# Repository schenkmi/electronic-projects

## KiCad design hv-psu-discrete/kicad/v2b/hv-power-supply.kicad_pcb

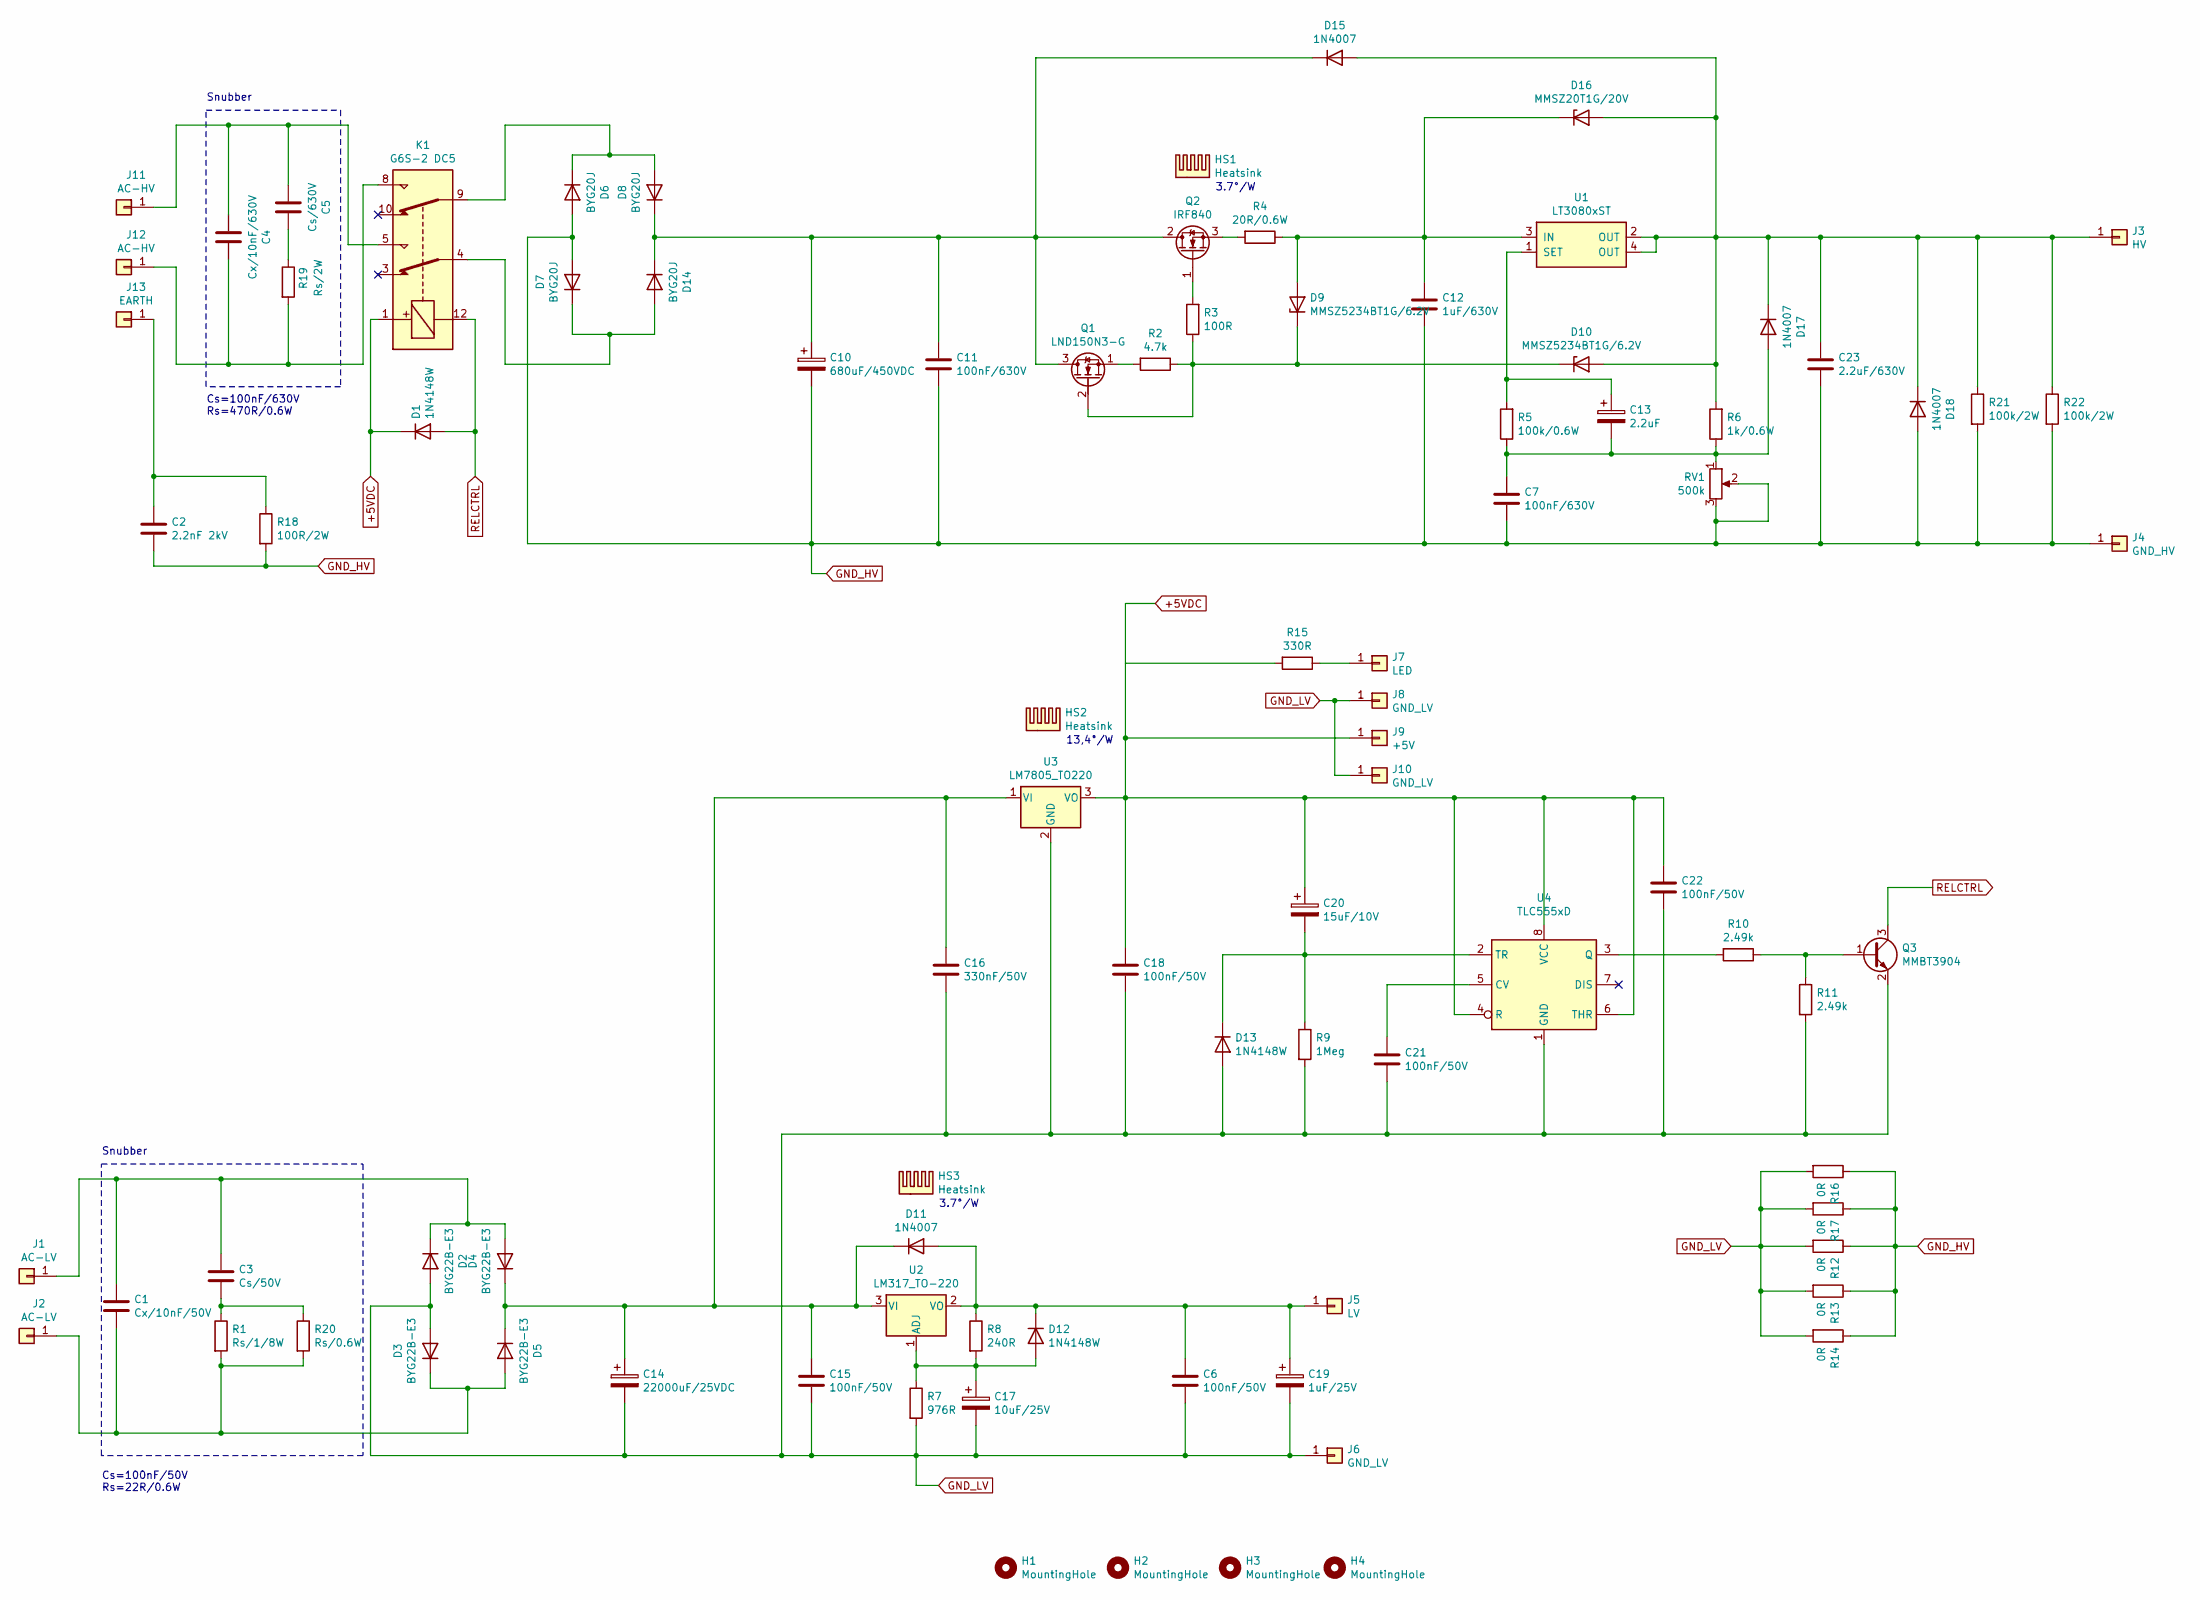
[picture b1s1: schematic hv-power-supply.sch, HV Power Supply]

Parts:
C1: Cx/10nF/50V; C_0805_2012Metric_Pad1.18x1.45mm_HandSolder
C2: 2.2nF 2kV; C_Rect_L18.0mm_W5.0mm_P15.00mm_FKS3_FKP3
C3: Cs/50V; C_0805_2012Metric_Pad1.18x1.45mm_HandSolder
C4: Cx/10nF/630V; C_Rect_L13.0mm_W4.0mm_P10.00mm_FKS3_FKP3_MKS4
C5: Cs/630V; C_Rect_L18.0mm_W5.0mm_P15.00mm_FKS3_FKP3
C6, C15, C18, C21, C22: 100nF/50V; C_0805_2012Metric_Pad1.18x1.45mm_HandSolder
C7, C11: 100nF/630V; C_Rect_L18.0mm_W5.0mm_P15.00mm_FKS3_FKP3
C10: 680uF/450VDC; CP_Radial_D35.0mm_P10.00mm_SnapIn
C12: 1uF/630V; C_Rect_L26.5mm_W10.5mm_P22.50mm_MKS4
C13: 2.2uF; CP_Radial_D5.0mm_P2.50mm
C14: 22000uF/25VDC; CP_Radial_D35.0mm_P10.00mm_SnapIn
C16: 330nF/50V; C_0805_2012Metric_Pad1.18x1.45mm_HandSolder
C17: 10uF/25V; CP_Radial_D5.0mm_P2.00mm
C19: 1uF/25V; CP_Radial_D5.0mm_P2.00mm
C20: 15uF/10V; CP_EIA-3216-12_Kemet-S_Pad1.58x1.35mm_HandSolder
C23: 2.2uF/630V; C_Rect_L33.0mm_W15.0mm_P27.50mm_MKS4
D1, D12, D13: 1N4148W; D_SOD-123
D2, D3, D4, D5: BYG22B-E3; D_SMA_Handsoldering
D6, D7, D8, D14: BYG20J; D_SMA_Handsoldering
D9, D10: MMSZ5234BT1G/6.2V; D_SOD-123
D11, D15, D17, D18: 1N4007; D_SMA_Handsoldering
D16: MMSZ20T1G/20V; D_SOD-123
H1, H2, H3, H4: MountingHole; MountingHole_3.2mm_M3
HS1, HS3: Heatsink; Heatsink_Fischer_SK129-STS_42x25mm_2xDrill2.5mm
HS2: Heatsink; Heatsink_Fischer_SK104-STC-STIC_35x13mm_2xDrill2.5mm
J1, J2: AC-LV; Pin_D1.3mm_L11.0mm
J3: HV; Pin_D1.3mm_L11.0mm
J4: GND_HV; Pin_D1.3mm_L11.0mm
J5: LV; Pin_D1.3mm_L11.0mm
J6: GND_LV; Pin_D1.3mm_L11.0mm
J7: LED; Pin_D1.0mm_L10.0mm
J8, J10: GND_LV; Pin_D1.0mm_L10.0mm
J9: +5V; Pin_D1.0mm_L10.0mm
J11, J12: AC-HV; Pin_D1.3mm_L11.0mm
J13: EARTH; Pin_D1.3mm_L11.0mm
K1: G6S-2 DC5; Relay_DPDT_Omron_G6S-2
Q1: LND150N3-G; SOT-89-3
Q2: IRF840; TO-220-3_Vertical
Q3: MMBT3904; SOT-23
R1: Rs/1/8W; R_0805_2012Metric_Pad1.20x1.40mm_HandSolder
R2: 4.7k; R_0805_2012Metric_Pad1.20x1.40mm_HandSolder
R3: 100R; R_0805_2012Metric_Pad1.20x1.40mm_HandSolder
R4: 20R/0.6W; R_Axial_DIN0207_L6.3mm_D2.5mm_P10.16mm_Horizontal
R5: 100k/0.6W; R_Axial_DIN0207_L6.3mm_D2.5mm_P10.16mm_Horizontal
R6: 1k/0.6W; R_Axial_DIN0207_L6.3mm_D2.5mm_P10.16mm_Horizontal
R7: 976R; R_0805_2012Metric_Pad1.20x1.40mm_HandSolder
R8: 240R; R_0805_2012Metric_Pad1.20x1.40mm_HandSolder
R9: 1Meg; R_0805_2012Metric_Pad1.20x1.40mm_HandSolder
R10, R11: 2.49k; R_0805_2012Metric_Pad1.20x1.40mm_HandSolder
R12, R13, R14, R16, R17: 0R; R_1206_3216Metric_Pad1.30x1.75mm_HandSolder
R15: 330R; R_0805_2012Metric_Pad1.20x1.40mm_HandSolder
R18: 100R/2W; R_Axial_DIN0414_L11.9mm_D4.5mm_P15.24mm_Horizontal
R19: Rs/2W; R_Axial_DIN0414_L11.9mm_D4.5mm_P15.24mm_Horizontal
R20: Rs/0.6W; R_Axial_DIN0207_L6.3mm_D2.5mm_P10.16mm_Horizontal
R21, R22: 100k/2W; R_Axial_DIN0414_L11.9mm_D4.5mm_P15.24mm_Horizontal
RV1: 500k; Potentiometer_Bourns_3296W_Vertical
U1: LT3080xST; SOT-223
U2: LM317_TO-220; TO-220-3_Vertical
U3: LM7805_TO220; TO-220-3_Vertical
U4: TLC555xD; SOIC-8_3.9x4.9mm_P1.27mm

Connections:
+5VDC: C18.1, C20.1, C22.1, D1.1 (K), J9.1, K1.1, R15.2, U3.3 (VO), U4.4 (R), U4.6 (THR), U4.8 (VCC)
GND_HV: C2.2, C7.2, C10.2, C11.2, C12.2, C23.2, D6.2 (A), D7.2 (A), D18.2 (A), J4.1, R12.1, R13.1, R14.1, R16.1, R17.1, R18.2, R21.2, R22.2, RV1.2, RV1.3
GND_LV: C6.2, C14.2, C15.2, C16.2, C17.2, C18.2, C19.2, C21.2, C22.2, D2.2 (A), D3.2 (A), D13.2 (A), J6.1, J8.1, J10.1, Q3.2 (E), R7.2, R9.2, R11.2, R12.2, R13.2, R14.2, R16.2, R17.2, U3.2 (GND), U4.1 (GND)
unnamed: C1.1, C3.1, D2.1 (K), D4.2 (A), J1.1
unnamed: C1.2, D3.1 (K), D5.2 (A), J2.1, R1.2, R20.2
unnamed: C2.1, J13.1, R18.1
unnamed: C3.2, R1.1, R20.1
unnamed: C4.1, J12.1, K1.8, R19.2
unnamed: C4.2, C5.2, J11.1, K1.5
unnamed: C5.1, R19.1
unnamed: C10.1, C11.1, D8.1 (K), D14.1 (K), D15.1 (K), Q1.3 (D), Q2.2 (D)
unnamed: C12.1, D9.2 (A), D16.1 (K), R4.1, U1.3 (IN)
unnamed: C13.1, R5.2, U1.1 (SET)
unnamed: C7.1, C13.2, D17.2 (A), R5.1, R6.1, RV1.1
unnamed: C14.1, C15.1, C16.1, D4.1 (K), D5.1 (K), D11.1 (K), U2.3 (VI), U3.1 (VI)
unnamed: C17.1, D12.2 (A), R7.1, R8.2, U2.1 (ADJ)
unnamed: C6.1, C19.1, D11.2 (A), D12.1 (K), J5.1, R8.1, U2.2 (VO)
unnamed: C20.2, D13.1 (K), R9.1, U4.2 (TR)
unnamed: C21.1, U4.5 (CV)
unnamed: C23.1, D10.2 (A), D15.2 (A), D16.2 (A), D17.1 (K), D18.1 (K), J3.1, R6.2, R21.1, R22.1, U1.2 (OUT), U1.4 (OUT)
unnamed: D6.1 (K), D8.2 (A), K1.9
unnamed: D9.1 (K), D10.1 (K), Q1.2 (G), R2.1, R3.1
unnamed: D7.1 (K), D14.2 (A), K1.4
unnamed: J7.1, R15.1
unnamed: Q1.1 (S), R2.2
unnamed: Q2.1 (G), R3.2
unnamed: Q2.3 (S), R4.2
unnamed: Q3.1 (B), R10.1, R11.1
unnamed: R10.2, U4.3 (Q)
RELCTRL: D1.2 (A), K1.12, Q3.3 (C)

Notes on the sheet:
Snubber
Cs=100nF/50V Rs=22R/0.6W
Cs=100nF/630V Rs=470R/0.6W
3.7°/W
13,4°/W

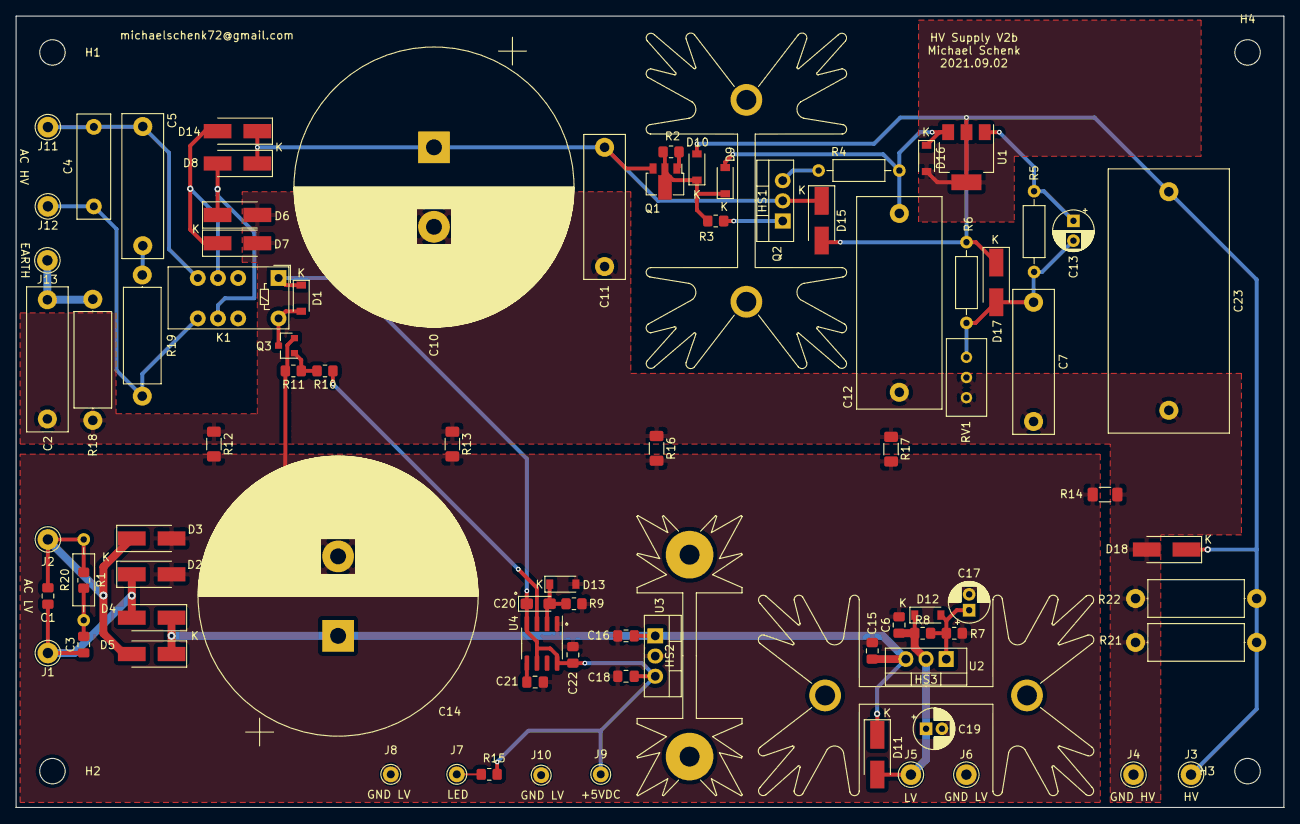
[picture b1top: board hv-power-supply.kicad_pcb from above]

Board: 2 copper layers, 159.5 x 99.6 mm, 90 parts (0 on the bottom side), 30 nets.

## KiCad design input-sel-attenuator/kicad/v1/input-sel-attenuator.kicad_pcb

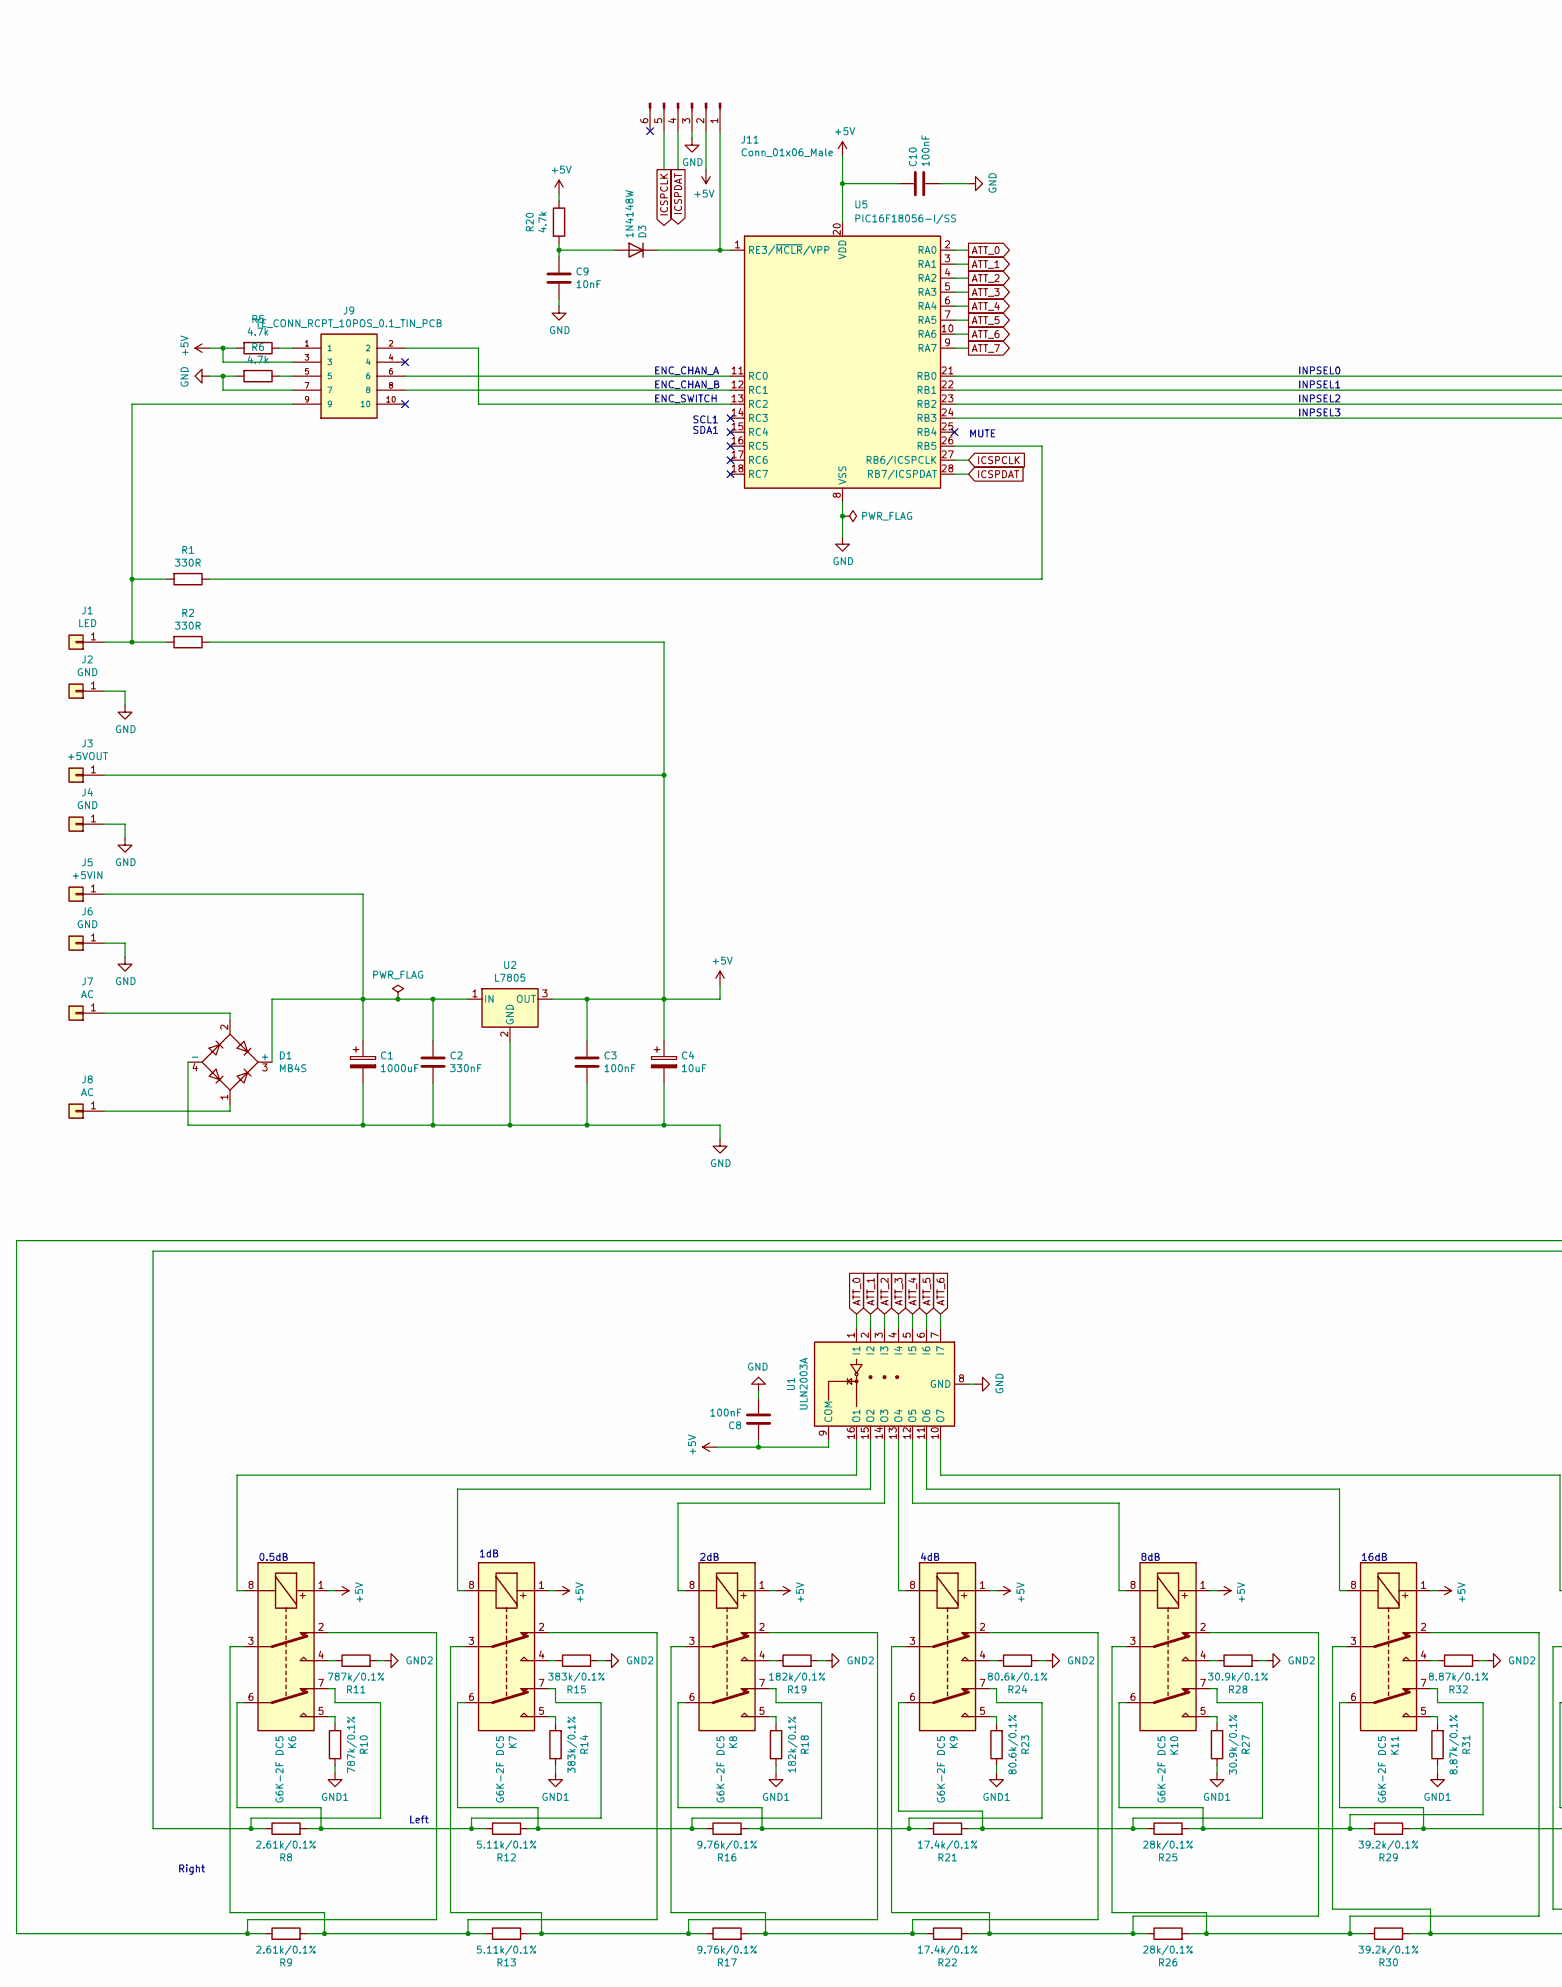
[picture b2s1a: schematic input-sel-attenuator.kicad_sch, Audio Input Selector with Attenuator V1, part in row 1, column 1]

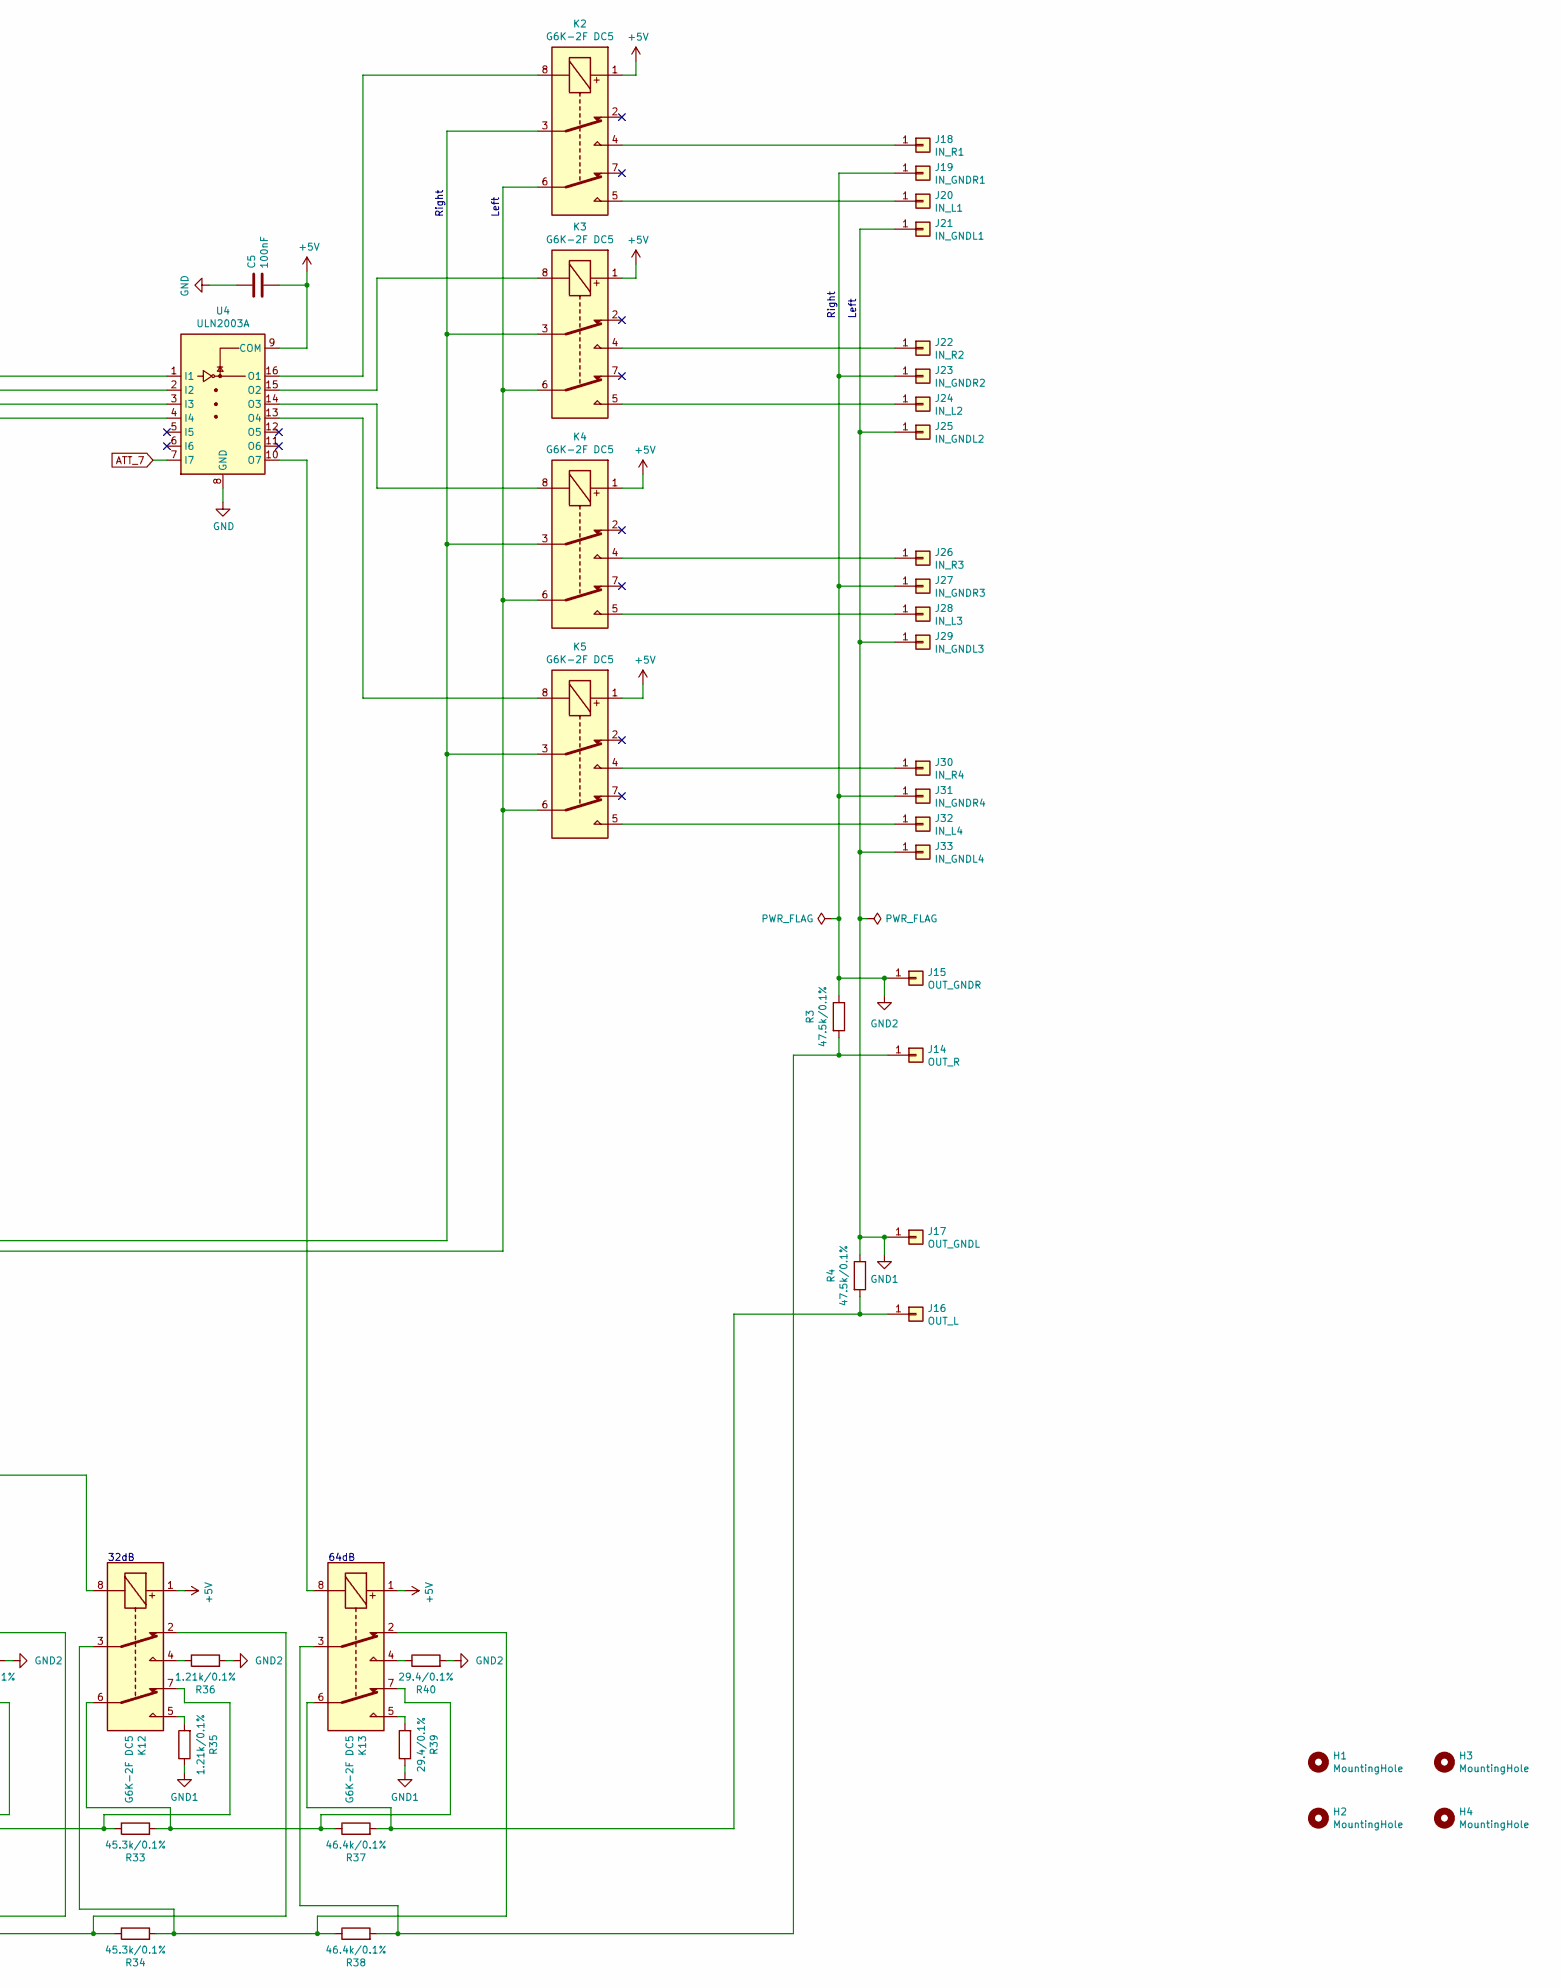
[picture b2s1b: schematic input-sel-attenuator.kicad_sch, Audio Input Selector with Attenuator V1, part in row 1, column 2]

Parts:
C1: 1000uF; CP_Radial_D12.5mm_P5.00mm
C2: 330nF; C_0805_2012Metric_Pad1.18x1.45mm_HandSolder
C3, C5, C8, C10: 100nF; C_0805_2012Metric_Pad1.18x1.45mm_HandSolder
C4: 10uF; CP_EIA-3528-21_Kemet-B_Pad1.50x2.35mm_HandSolder
C9: 10nF; C_0805_2012Metric_Pad1.18x1.45mm_HandSolder
D1: MB4S; TO-269AA
D3: 1N4148W; D_SOD-123
H1, H2, H3, H4: MountingHole; MountingHole_3.2mm_M3
J1: LED; Pin_D1.0mm_L10.0mm
J2, J4, J6: GND; Pin_D1.0mm_L10.0mm
J3: +5VOUT; Pin_D1.0mm_L10.0mm
J5: +5VIN; Pin_D1.0mm_L10.0mm
J7, J8: AC; Pin_D1.0mm_L10.0mm
J9: TE_CONN_RCPT_10POS_0.1_TIN_PCB
J11: Conn_01x06_Male; PinHeader_1x06_P2.54mm_Vertical
J14: OUT_R; Pin_D1.0mm_L10.0mm
J15: OUT_GNDR; Pin_D1.0mm_L10.0mm
J16: OUT_L; Pin_D1.0mm_L10.0mm
J17: OUT_GNDL; Pin_D1.0mm_L10.0mm
J18: IN_R1; Pin_D1.0mm_L10.0mm
J19: IN_GNDR1; Pin_D1.0mm_L10.0mm
J20: IN_L1; Pin_D1.0mm_L10.0mm
J21: IN_GNDL1; Pin_D1.0mm_L10.0mm
J22: IN_R2; Pin_D1.0mm_L10.0mm
J23: IN_GNDR2; Pin_D1.0mm_L10.0mm
J24: IN_L2; Pin_D1.0mm_L10.0mm
J25: IN_GNDL2; Pin_D1.0mm_L10.0mm
J26: IN_R3; Pin_D1.0mm_L10.0mm
J27: IN_GNDR3; Pin_D1.0mm_L10.0mm
J28: IN_L3; Pin_D1.0mm_L10.0mm
J29: IN_GNDL3; Pin_D1.0mm_L10.0mm
J30: IN_R4; Pin_D1.0mm_L10.0mm
J31: IN_GNDR4; Pin_D1.0mm_L10.0mm
J32: IN_L4; Pin_D1.0mm_L10.0mm
J33: IN_GNDL4; Pin_D1.0mm_L10.0mm
K2, K3, K4, K5, K6, K7, K8, K9, K10, K11, K12, K13: G6K-2F DC5; Relay_DPDT_Omron_G6K-2F
R1, R2: 330R; R_0805_2012Metric_Pad1.20x1.40mm_HandSolder
R3, R4: 47.5k/0.1%; R_0805_2012Metric_Pad1.20x1.40mm_HandSolder
R5, R6, R20: 4.7k; R_0805_2012Metric_Pad1.20x1.40mm_HandSolder
R8, R9: 2.61k/0.1%; R_0805_2012Metric_Pad1.20x1.40mm_HandSolder
R10, R11: 787k/0.1%; R_0805_2012Metric_Pad1.20x1.40mm_HandSolder
R12, R13: 5.11k/0.1%; R_0805_2012Metric_Pad1.20x1.40mm_HandSolder
R14, R15: 383k/0.1%; R_0805_2012Metric_Pad1.20x1.40mm_HandSolder
R16, R17: 9.76k/0.1%; R_0805_2012Metric_Pad1.20x1.40mm_HandSolder
R18, R19: 182k/0.1%; R_0805_2012Metric_Pad1.20x1.40mm_HandSolder
R21, R22: 17.4k/0.1%; R_0805_2012Metric_Pad1.20x1.40mm_HandSolder
R23, R24: 80.6k/0.1%; R_0805_2012Metric_Pad1.20x1.40mm_HandSolder
R25, R26: 28k/0.1%; R_0805_2012Metric_Pad1.20x1.40mm_HandSolder
R27, R28: 30.9k/0.1%; R_0805_2012Metric_Pad1.20x1.40mm_HandSolder
R29, R30: 39.2k/0.1%; R_0805_2012Metric_Pad1.20x1.40mm_HandSolder
R31, R32: 8.87k/0.1%; R_0805_2012Metric_Pad1.20x1.40mm_HandSolder
R33, R34: 45.3k/0.1%; R_0805_2012Metric_Pad1.20x1.40mm_HandSolder
R35, R36: 1.21k/0.1%; R_0805_2012Metric_Pad1.20x1.40mm_HandSolder
R37, R38: 46.4k/0.1%; R_0805_2012Metric_Pad1.20x1.40mm_HandSolder
R39, R40: 29.4/0.1%; R_0805_2012Metric_Pad1.20x1.40mm_HandSolder
U1, U4: ULN2003A; SOIC-16_3.9x9.9mm_P1.27mm
U2: L7805; TO-220-3_Vertical
U5: PIC16F18056-I/SS; SSOP-28_5.3x10.2mm_P0.65mm

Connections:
+5V: C3.1, C4.1, C5.2, C8.1, C10.1, J3.1, J9.3, J11.2, K2.1, K3.1, K4.1, K5.1, K6.1, K7.1, K8.1, K9.1, K10.1, K11.1, K12.1, K13.1, R2.1, R5.2, R20.1, U1.9 (COM), U2.3 (OUT), U4.9 (COM), U5.20 (VDD)
ATT_0: U1.1 (I1), U5.2 (RA0)
ATT_1: U1.2 (I2), U5.3 (RA1)
ATT_2: U1.3 (I3), U5.4 (RA2)
ATT_3: U1.4 (I4), U5.5 (RA3)
ATT_4: U1.5 (I5), U5.6 (RA4)
ATT_5: U1.6 (I6), U5.7 (RA5)
ATT_6: U1.7 (I7), U5.10 (RA6)
ATT_7: U4.7 (I7), U5.9 (RA7)
GND: C1.2, C2.2, C3.2, C4.2, C5.1, C8.2, C9.2, C10.2, D1.4 (-), J2.1, J4.1, J6.1, J9.7, J11.3, R6.2, U1.8 (GND), U2.2 (GND), U4.8 (GND), U5.8 (VSS), U5.19 (VSS)
GND1: J17.1, J21.1, J25.1, J29.1, J33.1, R4.1, R10.1, R14.1, R18.1, R23.1, R27.1, R31.1, R35.1, R39.1
GND2: J15.1, J19.1, J23.1, J27.1, J31.1, R3.1, R11.2, R15.2, R19.2, R24.2, R28.2, R32.2, R36.2, R40.2
ICSPCLK: J11.5, U5.27 (RB6/ICSPCLK)
ICSPDAT: J11.4, U5.28 (RB7/ICSPDAT)
unnamed: C1.1, C2.1, D1.3 (+), J5.1, U2.1 (IN)
unnamed: C9.1, D3.2 (A), R20.2
unnamed: D1.1, J8.1
unnamed: D1.2, J7.1
unnamed: D3.1 (K), J11.1, U5.1 (RE3/~MCLR/VPP)
unnamed: J1.1, J9.9, R1.2, R2.2
unnamed: J9.1, R5.1
unnamed: J9.2, U5.13 (RC2)
unnamed: J9.5, R6.1
unnamed: J9.6, U5.11 (RC0)
unnamed: J9.8, U5.12 (RC1)
unnamed: J14.1, K13.3, R3.2, R38.2
unnamed: J16.1, K13.6, R4.2, R37.2
unnamed: J18.1, K2.4
unnamed: J20.1, K2.5
unnamed: J22.1, K3.4
unnamed: J24.1, K3.5
unnamed: J26.1, K4.4
unnamed: J28.1, K4.5
unnamed: J30.1, K5.4
unnamed: J32.1, K5.5
unnamed: K2.3, K3.3, K4.3, K5.3, K6.2, R9.1
unnamed: K2.6, K3.6, K4.6, K5.6, K6.7, R8.1
unnamed: K2.8, U4.16 (O1)
unnamed: K3.8, U4.15 (O2)
unnamed: K4.8, U4.14 (O3)
unnamed: K5.8, U4.13 (O4)
unnamed: K6.3, K7.2, R9.2, R13.1
unnamed: K6.4, R11.1
unnamed: K6.5, R10.2
unnamed: K6.6, K7.7, R8.2, R12.1
unnamed: K6.8, U1.16 (O1)
unnamed: K7.3, K8.2, R13.2, R17.1
unnamed: K7.4, R15.1
unnamed: K7.5, R14.2
unnamed: K7.6, K8.7, R12.2, R16.1
unnamed: K7.8, U1.15 (O2)
unnamed: K8.3, K9.2, R17.2, R22.1
unnamed: K8.4, R19.1
unnamed: K8.5, R18.2
unnamed: K8.6, K9.7, R16.2, R21.1
unnamed: K8.8, U1.14 (O3)
unnamed: K9.4, R24.1
unnamed: K9.5, R23.2
unnamed: K9.8, U1.13 (O4)
unnamed: K9.3, K10.2, R22.2, R26.1
unnamed: K10.3, K11.2, R26.2, R30.1
unnamed: K10.4, R28.1
unnamed: K10.5, R27.2
unnamed: K10.6, K11.7, R25.2, R29.1
unnamed: K9.6, K10.7, R21.2, R25.1
unnamed: K10.8, U1.12 (O5)
unnamed: K11.3, K12.2, R30.2, R34.1
unnamed: K11.4, R32.1
unnamed: K11.5, R31.2
unnamed: K11.6, K12.7, R29.2, R33.1
unnamed: K11.8, U1.11 (O6)
unnamed: K12.3, K13.2, R34.2, R38.1
unnamed: K12.4, R36.1
unnamed: K12.5, R35.2
unnamed: K12.6, K13.7, R33.2, R37.1
unnamed: K12.8, U1.10 (O7)
unnamed: K13.4, R40.1
unnamed: K13.5, R39.2
unnamed: K13.8, U4.10 (O7)
unnamed: R1.1, U5.26 (RB5)
unnamed: U4.1 (I1), U5.21 (RB0)
unnamed: U4.2 (I2), U5.22 (RB1)
unnamed: U4.3 (I3), U5.23 (RB2)
unnamed: U4.4 (I4), U5.24 (RB3)

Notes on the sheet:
Right
2dB
8dB
INPSEL3
SCL1
Left
1dB
4dB
MUTE
ENC_SWITCH
SDA1
INPSEL0
ENC_CHAN_A
64dB
0.5dB
ENC_CHAN_B
16dB
INPSEL1
INPSEL2
32dB

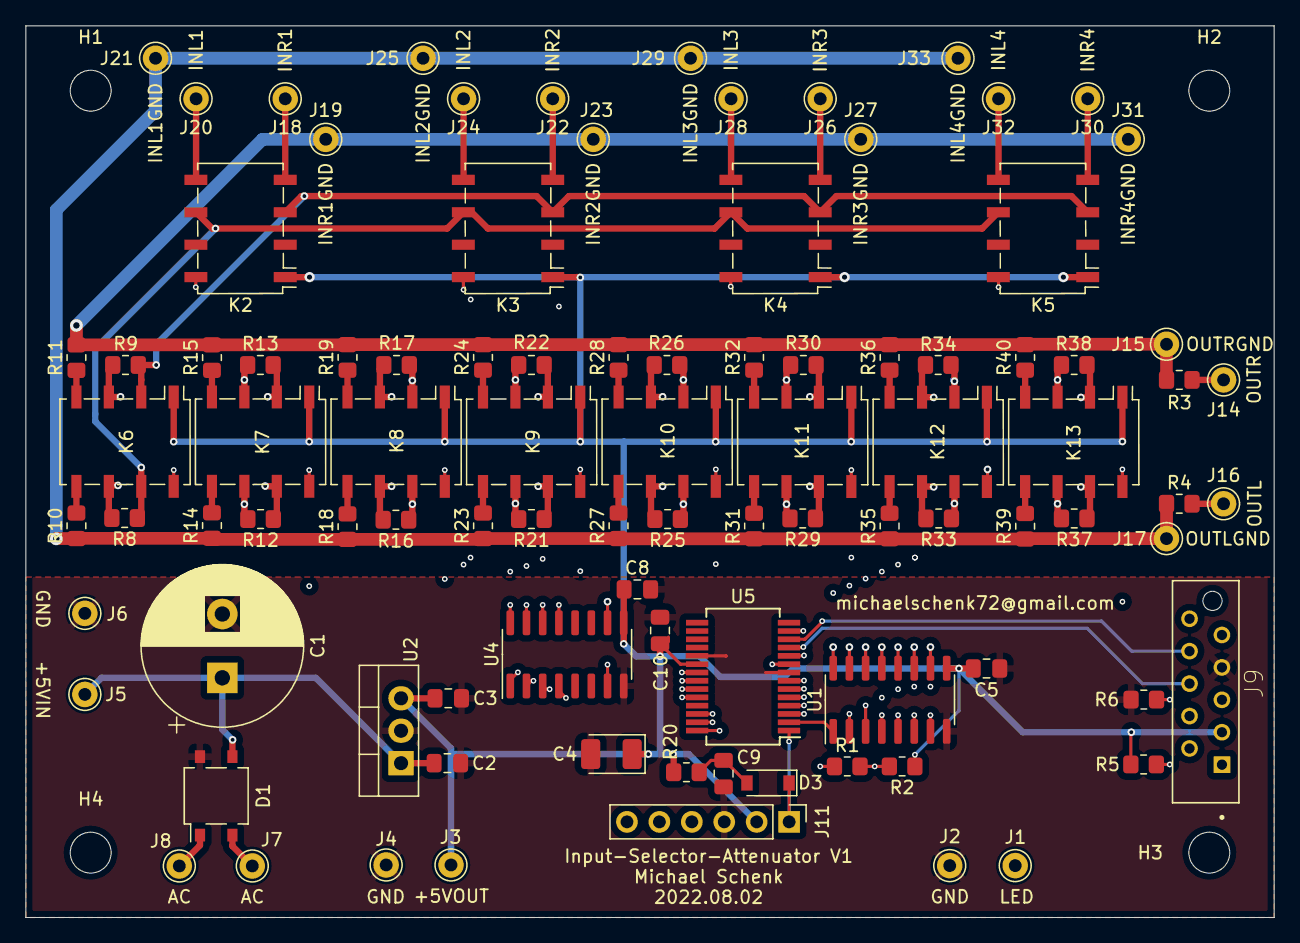
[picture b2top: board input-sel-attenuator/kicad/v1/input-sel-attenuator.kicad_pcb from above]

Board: 4 copper layers, 97.8 x 69.8 mm, 99 parts (0 on the bottom side), 84 nets.

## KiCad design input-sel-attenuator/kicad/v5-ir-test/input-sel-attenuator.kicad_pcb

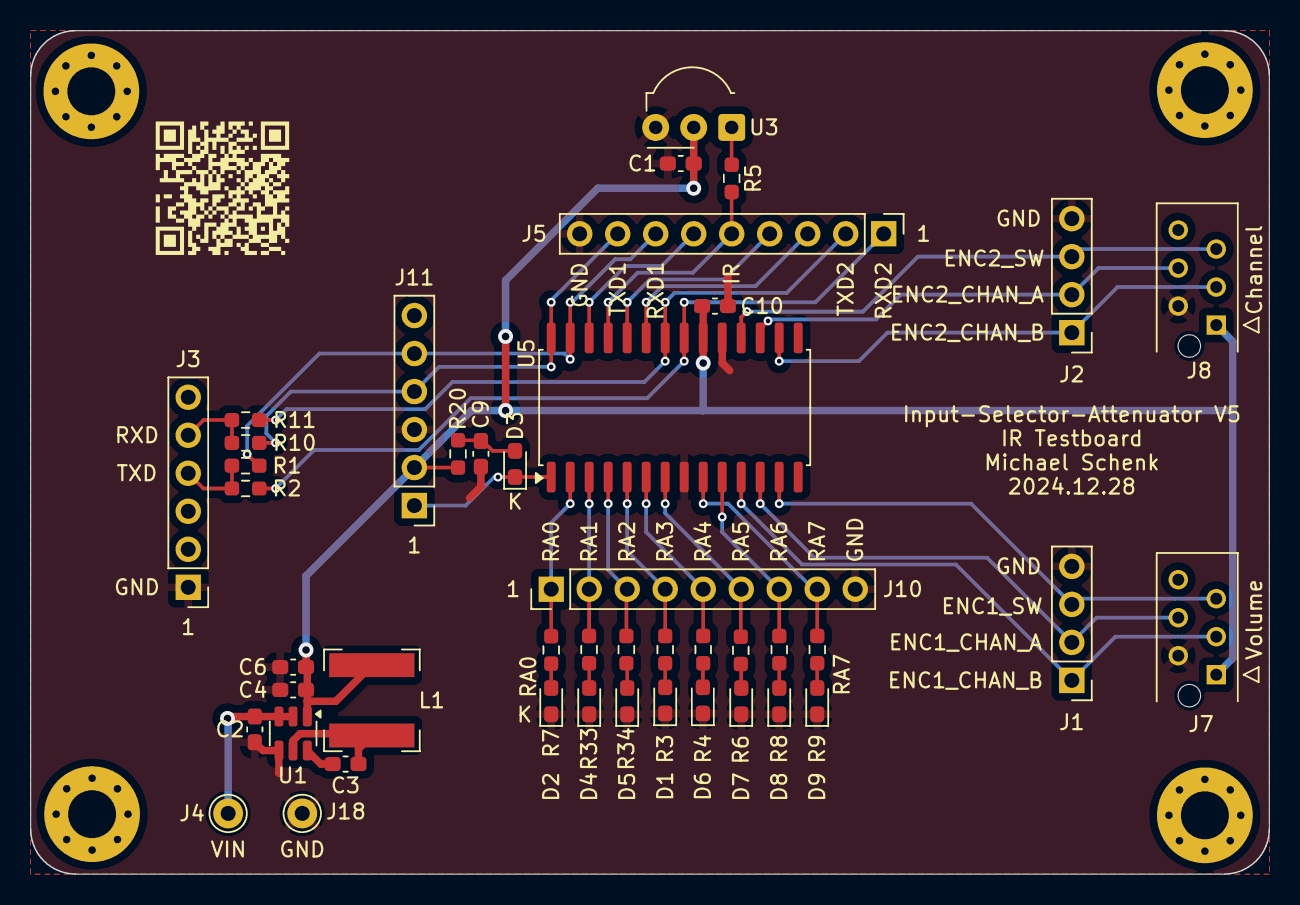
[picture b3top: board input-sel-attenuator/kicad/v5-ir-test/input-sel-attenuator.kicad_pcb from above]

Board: 2 copper layers, 82.8 x 56.4 mm, 48 parts (0 on the bottom side), 40 nets.

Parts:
C1: 100nF/50V; C_0603_1608Metric_Pad1.08x0.95mm_HandSolder
C2: 10uF/25V/X5R; C_0603_1608Metric_Pad1.08x0.95mm_HandSolder
C3: 100nF/50V/X7R; C_0603_1608Metric_Pad1.08x0.95mm_HandSolder
C4, C6: 22uF/10V/X5R; C_0603_1608Metric_Pad1.08x0.95mm_HandSolder
C9: 10nF; C_0603_1608Metric_Pad1.08x0.95mm_HandSolder
C10: 100nF; C_0603_1608Metric_Pad1.08x0.95mm_HandSolder
D1, D2, D4, D5, D6, D7, D8, D9: LED; LED_0603_1608Metric_Pad1.05x0.95mm_HandSolder
D3: TS4148RCG; D_0603_1608Metric_Pad1.05x0.95mm_HandSolder
H1, H2, H3, H4: MountingHole; MountingHole_3.2mm_M3_Pad_Via
J1, J2: Conn_01x04_Pin; PinHeader_1x04_P2.54mm_Vertical
J3: TTL-232R-3V3; PinHeader_1x06_P2.54mm_Vertical
J4, J18: Conn_01x01; Pin_D1.0mm_L10.0mm
J5, J10: Conn_01x09_Pin; PinHeader_1x09_P2.54mm_Vertical
J7, J8: TE MicroMatch; TE_Micro-MaTch_215079-6_2x03_P1.27mm_Vertical
J11: Conn_01x06_Male; PinHeader_1x06_P2.54mm_Vertical
L1: 3.9uH; L_Bourns-SRN6028
R1, R2, R5, R10, R11: 0R; R_0603_1608Metric_Pad0.98x0.95mm_HandSolder
R3, R4, R6, R7, R8, R9, R33, R34: 330R; R_0603_1608Metric_Pad0.98x0.95mm_HandSolder
R20: 4.7k; R_0603_1608Metric_Pad0.98x0.95mm_HandSolder
U1: AP63203WU-7; TSOT-23-6
U3: TSOP32538; Vishay_MOLD-3Pin
U5: PIC16F18056-I/SS; SOIC-28W_7.5x17.9mm_P1.27mm

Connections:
+3.3V: C1.2, C4.1, C6.1, C10.1, J7.1, J8.1, J11.2, L1.2, R20.1, U1.1 (FB), U3.2 (Vs), U5.20 (VDD)
/IRIN: J5.5, R5.2, U5.25 (RB4)
/RXD2: J5.1, R2.1, U5.21 (RB0)
/SWOUT: C3.1, L1.1, U1.5 (SW)
/TXD2: J5.2, R11.1, U5.22 (RB1)
/VIN: C2.1, J4.1, U1.2 (EN), U1.3 (IN)
GND: C1.1, C2.2, C4.2, C6.2, C9.2, C10.2, D1.1 (K), D2.1 (K), D4.1 (K), D5.1 (K), D6.1 (K), D7.1 (K), D8.1 (K), D9.1 (K), J1.4, J2.4, J3.1, J5.9, J7.2, J8.2, J10.9, J11.3, J18.1, U1.4 (GND), U3.3 (GND), U5.8 (VSS), U5.19 (VSS)
ICSPCLK: J5.7, J11.5, R1.1, U5.27 (RB6/ICSPCLK)
ICSPDAT: J5.8, J11.4, R10.1, U5.28 (RB7/ICSPDAT)
unnamed: D1.2 (A), R3.2
unnamed: D2.2 (A), R7.2
unnamed: C9.1, D3.2 (A), R20.2
unnamed: D3.1 (K), J11.1, U5.1 (RE3/~MCLR/VPP)
unnamed: D4.2 (A), R33.2
unnamed: D5.2 (A), R34.2
unnamed: D6.2 (A), R4.2
unnamed: D7.2 (A), R6.2
unnamed: D8.2 (A), R8.2
unnamed: D9.2 (A), R9.2
unnamed: J3.4, R1.2, R2.2
unnamed: J3.5, R10.2, R11.2
unnamed: J5.3, U5.23 (RB2)
unnamed: J5.4, U5.24 (RB3)
unnamed: J5.6, U5.26 (RB5)
unnamed: J10.1, R7.1, U5.2 (RA0)
unnamed: J10.2, R33.1, U5.3 (RA1)
unnamed: J10.3, R34.1, U5.4 (RA2)
unnamed: J10.4, R3.1, U5.5 (RA3)
unnamed: J10.5, R4.1, U5.6 (RA4)
unnamed: J10.6, R6.1, U5.7 (RA5)
unnamed: J10.7, R8.1, U5.10 (RA6)
unnamed: J10.8, R9.1, U5.9 (RA7)
unnamed: C3.2, U1.6 (BST)
unnamed: R5.1, U3.1 (OUT)
RC0/CHA: J1.1, J7.3, U5.11 (RC0)
RC1/CHB: J1.2, J7.4, U5.12 (RC1)
RC2/SW: J1.3, J7.5, U5.13 (RC2)
RC5/CHA: J2.1, J8.3, U5.16 (RC5)
RC6/CHB: J2.2, J8.4, U5.17 (RC6)
RC7/SW: J2.3, J8.5, U5.18 (RC7)
